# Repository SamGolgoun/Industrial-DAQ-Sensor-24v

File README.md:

# Industrial DAQ Sensor 24V

4-layer industrial sensor and data acquisition (DAQ) node designed in KiCad around **STM32G431CBUx**, powered from a **24V** supply via **TPS54302** buck regulator, featuring **CAN FD** (**TCAN332**), **4–20mA** analog input, and **TMP101** + **LIS3DH** sensors.

## Completed Work
- **Schematic & Protection:** Finalized STM32G431CBUx schematic with TPS54302 (24V step-down), SMBJ28A TVS protection, Zener clamps, TCAN332 CAN FD transceiver, 4–20mA analog input conditioning, TMP101 temperature sensor, and LIS3DH accelerometer.
- **Footprints & Mechanical Design:** Assigned SMD footprints, added isolated M3 mounting holes (`MountingHole_3.2mm_M3_Pad` unconnected to nets to prevent ground loops), and placed fiducial markers.
- **4-Layer PCB Setup & Initial Layout:** Configured 4-layer stackup (`F.Cu`, `In1.Cu` for `GND`, `In2.Cu` for power rails, `B.Cu`), set Design Rules (`Constraints` and `Pre-defined Sizes`), and started `Edge.Cuts` and component placement in KiCad PCB Editor.

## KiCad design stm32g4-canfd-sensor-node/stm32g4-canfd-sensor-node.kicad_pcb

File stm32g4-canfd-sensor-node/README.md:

# Industrial DAQ Sensor Node (24V) — STM32G4 CAN-FD PCB Design

## Overview & Purpose
This project designs a **24V industrial sensor and data acquisition (DAQ) node** in **KiCad** built around the **STM32G431CBUx (UFQFPN48)** microcontroller and a **TCAN332 CAN-FD transceiver** for industrial sensing and CAN-FD communication.

## Current Status
- **Schematic:** Finalized and included in the repository.
- **PCB Layout (In Progress):** The `.kicad_pcb` layout is being routed and validated using an **AI-assisted, code-driven workflow** in **VS Code** with **Python** scripts rather than manual GUI-only edits.

## Key Engineering Features
- **Code-Driven & AI-Assisted Workflow:** Routing steps, geometry checks, and rule gates are scripted in Python inside VS Code with AI assistant tools.
- **Safety & Pre-Write Rule Gates:** Timestamped backups are created before edits; pre-write checks enforce component and courtyard clearance, forbid routing over component bodies or courtyards, prevent unintended `GND` shorts, and verify parenthesis balance.
- **Stepped Trace Widths & Angles:** Narrow exits step up to wider widths in open corridors where clearance is satisfied, avoiding sharp acute angles (`< 90°`).
- **Verification:** Scripts are syntax-checked (`python3 -m py_compile`) and paired with DRC checks and copper zone refills (`B`) in KiCad.

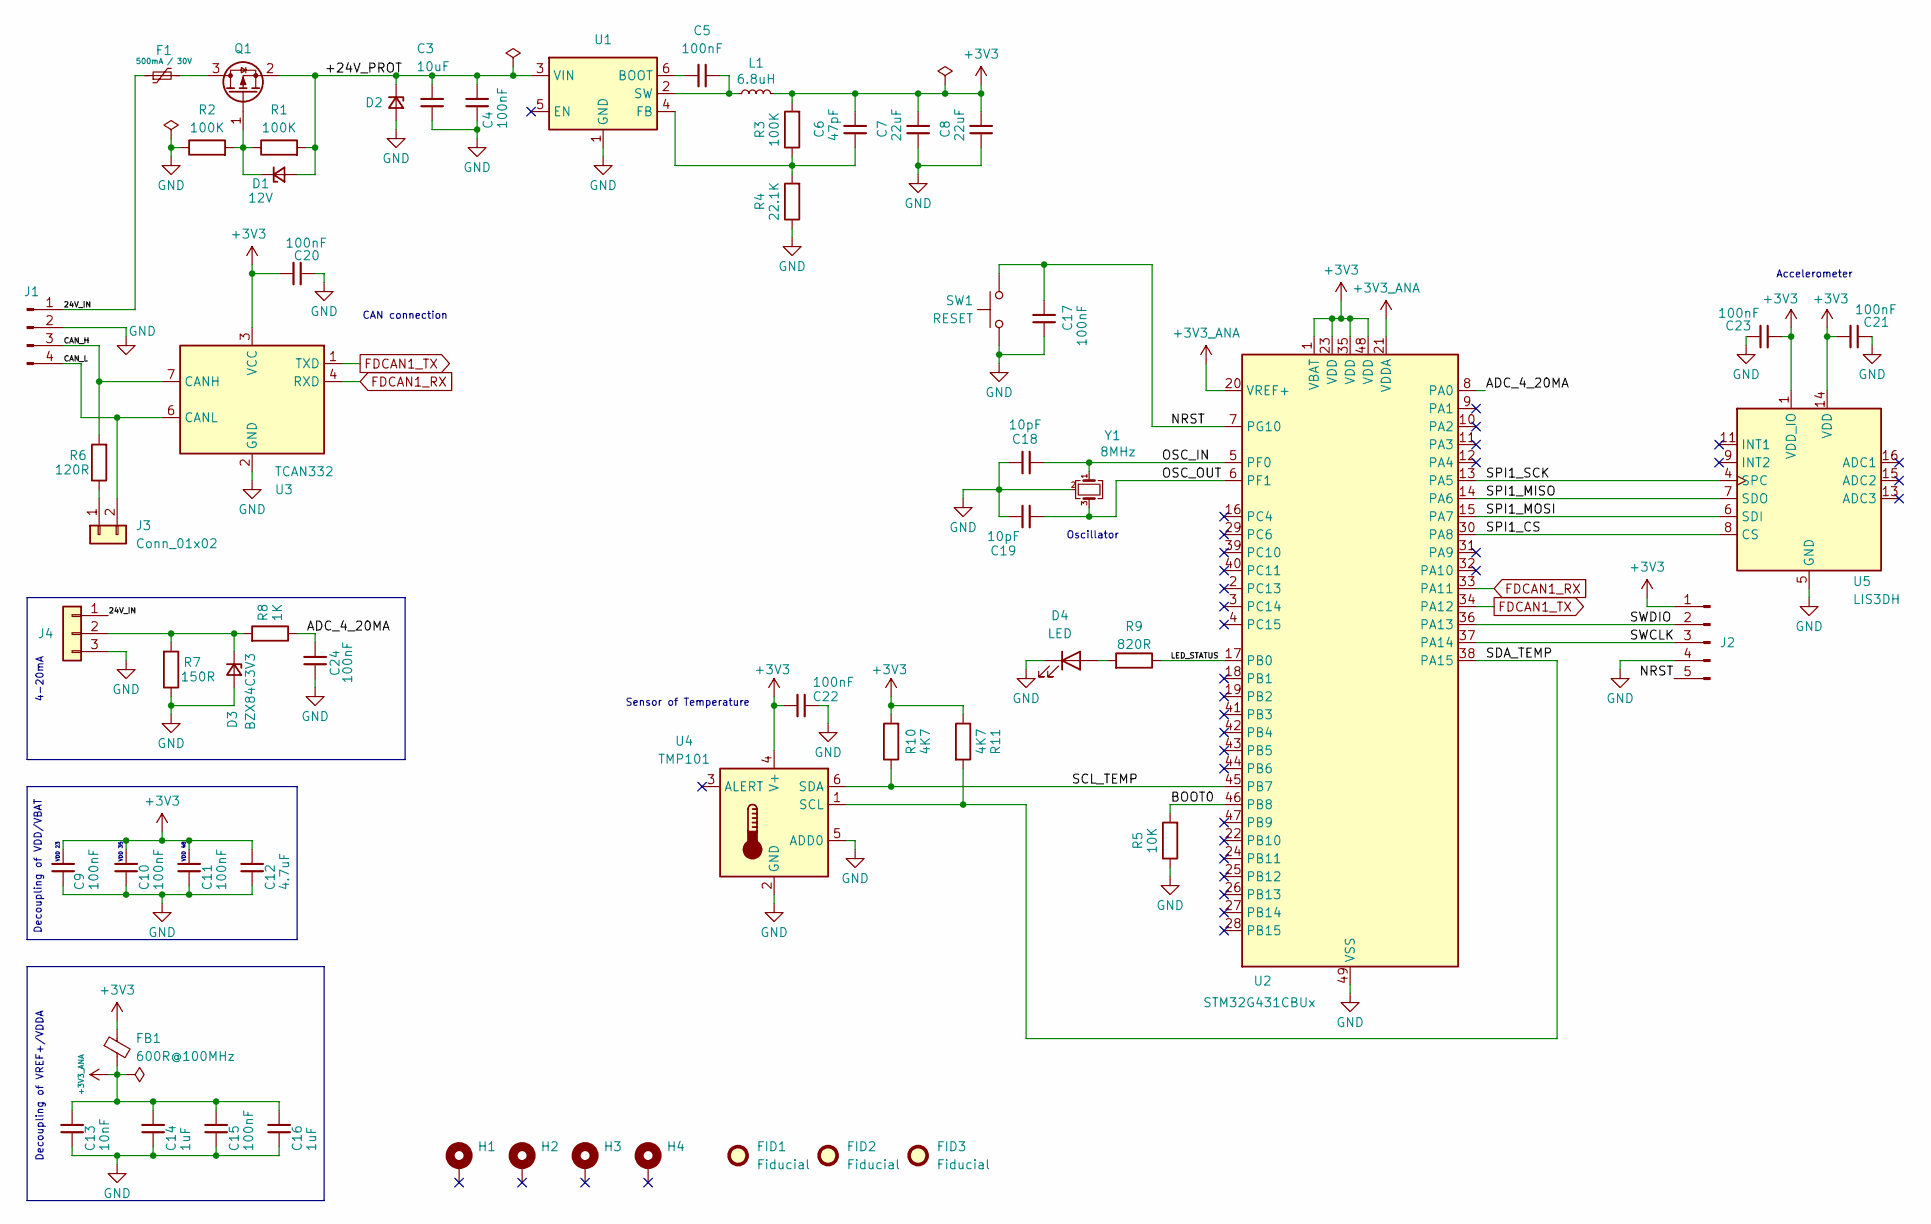
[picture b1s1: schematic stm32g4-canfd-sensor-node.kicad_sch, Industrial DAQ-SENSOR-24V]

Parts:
C3: 10uF; C_1206_3216Metric
C4, C5, C9, C10, C11, C15, C17, C20, C21, C22, C23, C24: 100nF; C_0603_1608Metric
C6: 47pF; C_0603_1608Metric
C7, C8: 22uF; C_0805_2012Metric
C12: 4.7uF; C_1206_3216Metric
C13: 10nF; C_0603_1608Metric
C14, C16: 1uF; C_1206_3216Metric
C18, C19: 10pF; C_0603_1608Metric
D1: 12V; D_SOD-123
D2: SMBJ28A; D_SMB
D3: BZX84C3V3; D_SOD-123
D4: LED; LED_0603_1608Metric
F1: 500mA / 30V; Fuse_1206_3216Metric
FB1: 600R@100MHz; L_0603_1608Metric
FID1, FID2, FID3: Fiducial; Fiducial_1mm_Mask2mm
H1, H2, H3, H4: MountingHole_Pad; MountingHole_3.2mm_M3_Pad
J1: Conn_01x04_Pin; PinHeader_1x04_P2.54mm_Vertical
J2: Conn_01x05_Pin; PinHeader_1x05_P2.54mm_Vertical
J3: Conn_01x02; PinHeader_1x02_P2.54mm_Vertical
J4: Conn_01x03; PinHeader_1x03_P2.54mm_Vertical
L1: 6.8uH; L_TDK_VLS6045EX_VLS6045AF
Q1: SI2319CDS; SOT-23
R1, R2, R3: 100K; R_0603_1608Metric
R4: 22.1K; R_0603_1608Metric
R5: 10K; R_0603_1608Metric
R6: 120R; R_0603_1608Metric
R7: 150R; R_0603_1608Metric
R8: 1K; R_0603_1608Metric
R9: 820R; R_0603_1608Metric
R10, R11: 4K7; R_0603_1608Metric
SW1: RESET; SW_SPST_PTS645Sx43SMTR92
U1: TPS54302; SOT-23-6
U2: STM32G431CBUx; QFN-48-1EP_7x7mm_P0.5mm_EP5.6x5.6mm
U3: TCAN332; SOT-23-6
U4: TMP101; SOT-23-6
U5: LIS3DH; LGA-16_3x3mm_P0.5mm_LayoutBorder3x5y
Y1: 8MHz; Crystal_SMD_3225-4Pin_3.2x2.5mm

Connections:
+3V3: C6.2, C7.2, C8.2, C9.2, C10.2, C11.2, C12.2, C20.2, C21.2, C22.1, C23.2, FB1.1, J2.1, L1.2, R3.2, R10.2, R11.1, U2.1 (VBAT), U2.23 (VDD), U2.35 (VDD), U2.48 (VDD), U3.3 (VCC), U4.4 (V+), U5.1 (VDD_IO), U5.14 (VDD)
+3V3_ANA: C13.2, C14.2, C15.2, C16.2, FB1.2, U2.20 (VREF+), U2.21 (VDDA)
/24V_IN: F1.1, J1.1, J4.1
/+24V_PROT: C3.2, C4.2, D1.2 (A), D2.1 (K), Q1.2 (S), R1.2, U1.3 (VIN)
/ADC_4_20MA: C24.2, R8.1, U2.8 (PA0)
/BOOT0: R5.2, U2.46 (PB8)
/CAN_H: J1.3, R6.2, U3.7 (CANH)
/CAN_L: J1.4, J3.2, U3.6 (CANL)
/LED_STATUS: R9.1, U2.17 (PB0)
/OSC_IN: C18.1, U2.5 (PF0), Y1.1
/OSC_OUT: C19.1, U2.6 (PF1), Y1.3
/SCL_TEMP: R10.1, U2.45 (PB7), U4.6 (SDA)
/SDA_TEMP: R11.2, U2.38 (PA15), U4.1 (SCL)
/SPI1_CS: U2.30 (PA8), U5.8 (CS)
/SPI1_MISO: U2.14 (PA6), U5.7 (SDO)
/SPI1_MOSI: U2.15 (PA7), U5.6 (SDI)
/SPI1_SCK: U2.13 (PA5), U5.4 (SPC)
/SWCLK: J2.3, U2.37 (PA14)
/SWDIO: J2.2, U2.36 (PA13)
FDCAN1_RX: U2.33 (PA11), U3.4 (RXD)
FDCAN1_TX: U2.34 (PA12), U3.1 (TXD)
GND: C3.1, C4.1, C7.1, C8.1, C9.1, C10.1, C11.1, C12.1, C13.1, C14.1, C15.1, C16.1, C17.1, C18.2, C19.2, C20.1, C21.1, C22.2, C23.1, C24.1, D2.2 (A), D3.2 (A), D4.1 (K), J1.2, J2.4, J4.3, R2.1, R4.1, R5.1, R7.1, SW1.1, U1.1 (GND), U2.49 (VSS), U3.2 (GND), U4.2 (GND), U4.5 (ADD0), U5.5 (GND), U5.10 (GND), U5.12 (GND), Y1.2 (G), Y1.4 (G)
NRST: C17.2, J2.5, SW1.2, U2.7 (PG10)
unnamed: D1.1 (K), Q1.1 (G), R1.1, R2.2
unnamed: D3.1 (K), J4.2, R7.2, R8.2
unnamed: D4.2 (A), R9.2
unnamed: J3.1, R6.1
unnamed: F1.2, Q1.3 (D)
unnamed: C5.1, U1.6 (BOOT)
unnamed: C6.1, R3.1, R4.2, U1.4 (FB)
unnamed: C5.2, L1.1, U1.2 (SW)

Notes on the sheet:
Decoupling of VDD/VBAT
CAN connection
Decoupling of VREF+/VDDA
Sensor of Temperature
VDD 23
Accelerometer
VDD 48
4-20mA
VDD 35
Oscillator

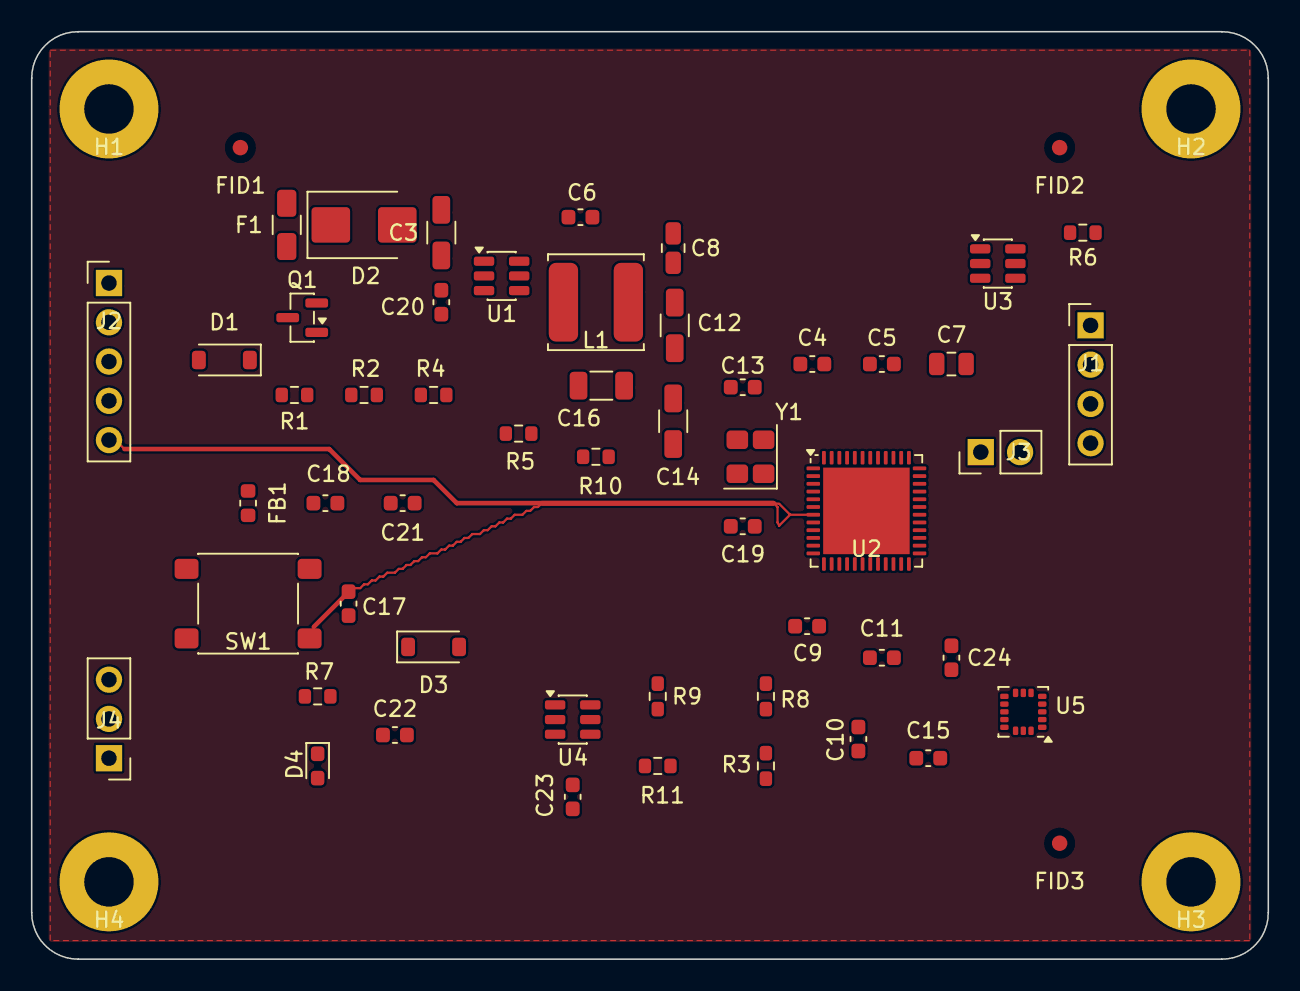
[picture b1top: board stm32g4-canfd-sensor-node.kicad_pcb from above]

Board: 4 copper layers, 80.0 x 60.0 mm, 59 parts (0 on the bottom side), 31 nets.

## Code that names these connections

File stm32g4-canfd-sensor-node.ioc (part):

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Mcu.Name=STM32G431C(6-8-B)Ux
Mcu.Package=UFQFPN48
Mcu.UserName=STM32G431CBUx
PA0.Mode=IN1-Single-Ended
PA0.Signal=ADC1_IN1
PA11.Mode=FDCAN_Activate
PA11.Signal=FDCAN1_RX
PA12.Mode=FDCAN_Activate
PA12.Signal=FDCAN1_TX
PA13.Mode=Serial_Wire
PA13.Signal=SYS_JTMS-SWDIO
PA14.Mode=Serial_Wire
PA14.Signal=SYS_JTCK-SWCLK
PA15.Mode=I2C
PA15.Signal=I2C1_SCL
PA5.Mode=Full_Duplex_Master
PA5.Signal=SPI1_SCK
PA6.Mode=Full_Duplex_Master
PA6.Signal=SPI1_MISO
PA7.Mode=Full_Duplex_Master
PA7.Signal=SPI1_MOSI
PA8.GPIOParameters=PinState,GPIO_Label
PA8.GPIO_Label=SPI1_CS
PA8.PinState=GPIO_PIN_SET
PA8.Signal=GPIO_Output
PB0.GPIOParameters=GPIO_Label
PB0.GPIO_Label=LED_STATUS
PB0.Signal=GPIO_Output
PB7.Mode=I2C
PB7.Signal=I2C1_SDA
RCC.HSE_VALUE=8000000
RCC.SYSCLKFreq_VALUE=16000000
board=custom
